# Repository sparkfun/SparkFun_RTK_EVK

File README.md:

SparkFun RTK EVK
========================================

[*SparkFun RTK EVK (GPS-24342)*](https://www.sparkfun.com/sparkfun-rtk-evk.html)

Designed and manufactured in Boulder, Colorado, USA, the SparkFun RTK Evaluation Kit is the perfect development platform for your fixed or mobile high-precision positioning and navigation needs. In terms of connectivity, the SparkFun RTK EVK has the lot: WiFi / BT, Ethernet and cellular!

Under the hood, the RTK EVK is based on the Espressif ESP32-WROVER processor with 16MB flash and 8MB PSRAM. The GNSS is the excellent dual-band ZED-F9P from u-blox. The u-blox NEO-D9S provides L-Band reception and access to correction services such as PointPerfect. The u-blox LARA-R6001D provides worldwide cellular connectivity; insert your nano SIM into the front panel and away you go! A WIZnet W5500 provides 10 / 100 megabit Ethernet connectivity. Data storage is micro-SD. The OLED display is 128x64 pixels. The EVK supports multiple power options, including: USB-C; Power over Ethernet (PoE); and DC voltages in the range 9V - 36V. 

Documentation
--------------

* **[Hookup Guide](http://docs.sparkfun.com/SparkFun_RTK_EVK/)** - Hookup Guide for the RTK EVK hosted by GitHub pages.
* **[RTK Everywhere Product Manual](https://docs.sparkfun.com/SparkFun_RTK_Everywhere_Firmware/)** - RTK Everywhere product manual hosted by GitHub Pages.

*Need to download or print our hookup guide?*

* [Print *(Print to PDF)* from Single-Page View](http://docs.sparkfun.com/SparkFun_RTK_EVK/print_view)

Repository Contents
-------------------

* **[/docs](/docs/)** - Online documentation files
    * **[assets](/docs/assets/)** - Assets files
        * **[RTK_EVK_Enclosure](/docs/assets/RTK_EVK_Enclosure/)**
            * **[/Front_Panel](/Front_Panel/)** - Eagle design files (.brd, .sch) for the prototype (PCB) enclosure panel used to validate the dimensions
            * **[/Front_Sticker](/Front_Sticker/)** - DXF and PDF files for the front sticker
            * **[/Rear_Panel](/Rear_Panel/)** - Eagle design files (.brd, .sch) for the prototype (PCB) enclosure panel used to validate the dimensions
            * **[/Rear_Sticker](/Rear_Sticker/)** - DXF and PDF files for the rear sticker
        * **[board_files](/docs/assets/board_files/)** - Files for the product design
        * **[img/](/docs/assets/img/hookup_guide/)** - Images for hookup guide documentation
* **[/Example_Sketches](/Example_Sketches/)** - Arduino IDE code examples
* **[/Hardware](/Hardware/)** - Eagle design files (.brd, .sch)
* **[/Production](/Production/)** - PCB panel production files

Firmware
----------------

The RTK Everywhere firmware has its own [dedicated repo](https://github.com/sparkfun/SparkFun_RTK_Everywhere_Firmware) as listed below.

* **[RTK Everywhere Firmware](https://github.com/sparkfun/SparkFun_RTK_Everywhere_Firmware)**
* **[RTK Everywhere Firmware Binaries](https://github.com/sparkfun/SparkFun_RTK_Everywhere_Firmware_Binaries)**

Product Variants
----------------

* [GPS-24342](https://www.sparkfun.com/sparkfun-rtk-evk.html)- v1.1, Initial Release

Version History
---------------

* v1.1- Initial Release

License Information
-------------------

This product is ***open source***!

Please review the [LICENSE.md](./LICENSE.md) file for license information.

If you have any questions or concerns about licensing, please contact technical support on our [SparkFun forums](https://forum.sparkfun.com/viewforum.php?f=152).

Distributed as-is; no warranty is given.

- Your friends at SparkFun.

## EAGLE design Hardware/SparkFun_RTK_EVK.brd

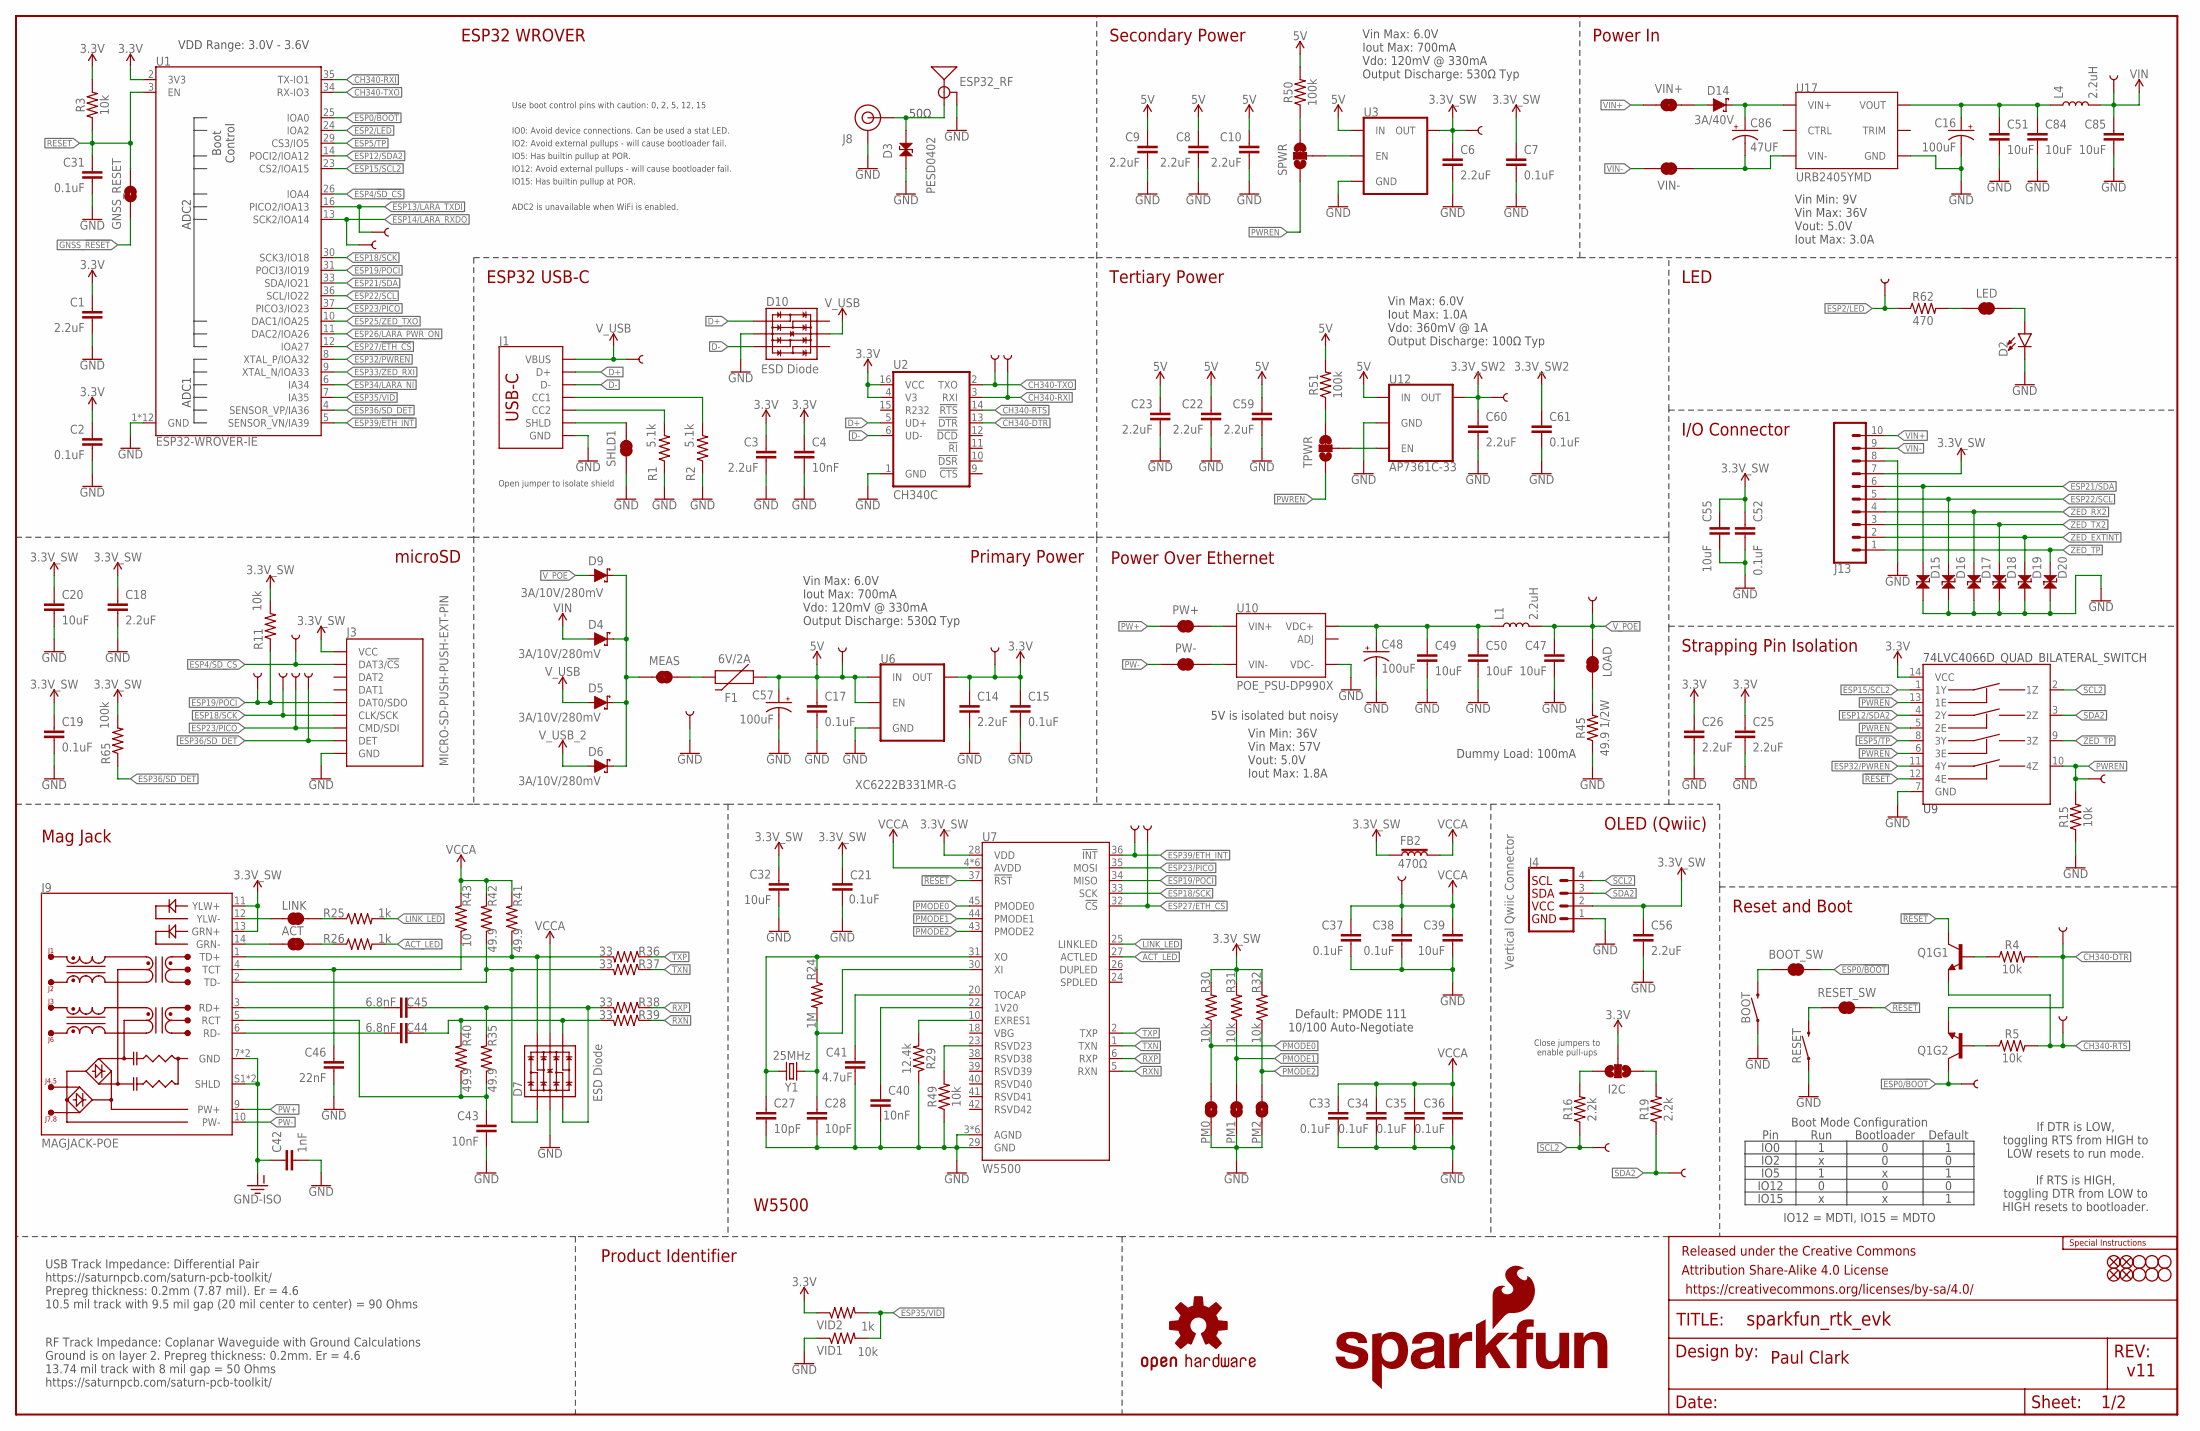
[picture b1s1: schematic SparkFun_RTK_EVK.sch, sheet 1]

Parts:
3V3, 3V3_SW, 3V3_SW2, 5V: TEST-POINTPOGO_PTH; 1X01_NO_SILK
ACT: JUMPER-SMT_2_NC_TRACE_SILK; SMT-JUMPER_2_NC_TRACE_SILK
BOOT: MOMENTARY-SWITCH-SPST-PTH-RIGHT-ANGLE-8-020; TACTILE_SWITCH_PTH_RA_8-020
BOOT_SW: JUMPER-SMT_2_NC_TRACE_SILK; SMT-JUMPER_2_NC_TRACE_SILK
C1, C3, C6, C8, C9, C10, C14, C18, C22, C23, C25, C26, C56, C59, C60: 2.2uF; 0603
C2, C7, C15, C17, C19, C21, C31, C33, C34, C35, C36, C37, C38, C52, C61: 0.1uF; 0603
C4, C40, C43: 10nF; 0603
C16, C48, C57: 100uF; PANASONIC_D
C20, C32, C39, C55: 10uF; 0603
C27, C28: 10pF; 0603
C41: 4.7uF; 0603
C42: 1nF; 1206
C44, C45: 6.8nF; 0603
C46: 22nF; 0603
C47, C49, C50, C51, C84, C85: 10uF; 0805
C86: 47UF; PANASONIC_D
D2: LED-RIGHT-ANGLE-PTH-GREEN; CBI-RIGHT-ANGLE-PTH
D3: PESD0402; 0402
D4, D5, D6, D9: 3A/10V/280mV; SOD-323
D7, D10: ESD Diode; SOT-23-6
D14: 3A/40V; SMA-DIODE
D15, D16, D17, D18, D19, D20: PESD0402-0402; 0402
DET: TEST-POINTPOGO_PTH; 1X01_NO_SILK
DTR: TEST-POINTPOGO_PTH; 1X01_NO_SILK
ESP32_RF: ANTENNA-SMA-GROUNDEDEDGE_RPSMA; RP-SMA-EDGE
ETH_CS: TEST-POINTPOGO_PTH; 1X01_NO_SILK
ETH_INT: TEST-POINTPOGO_PTH; 1X01_NO_SILK
F1: 6V/2A; 1210
FB2: 470Ω; 0603
FD1, FD2, FD3, FD4: FIDUCIAL1X2; FIDUCIAL-1X2
FRAME1: FRAME-LEDGER; CREATIVE_COMMONS
GND: TEST-POINTPOGO_PTH; 1X01_NO_SILK
GNSS_RESET: JUMPER-COMBO_2_NO; COMBO-JUMPER_2_NO
H1, H2, H3, H4, H5, H6: STAND-OFFTIGHT; STAND-OFF-TIGHT
I2C: JUMPER-SMT_3_NO_SILK; SMT-JUMPER_3_NO_SILK
J1: USB_C_4-LAYER_PADS; USB-C-16P_4LAYER-PADS
J3: MICRO-SD-PUSH-PUSH-EXT-PIN; MICROSD-EXTERNALPIN
J4: Vertical Qwiic Connector; JST04_1MM_VERT
J8: U.FL2PIN-REDUCED-FOOTPRINT; U.FL_REDUCED_FOOTPRINT
J9: MAGJACK-POE; MAGJACK-SYM_LED
J13: CONN_10_3.5MM_RA_HEADER; 1X10_SCREW_TERMINAL_3.5MM
L1, L4: 2.2uH; 0805-WIDE
LED: JUMPER-SMT_2_NC_TRACE_SILK; SMT-JUMPER_2_NC_TRACE_SILK
LINK: JUMPER-SMT_2_NC_TRACE_SILK; SMT-JUMPER_2_NC_TRACE_SILK
LOAD: JUMPER-SMT_2_NC_TRACE_SILK; SMT-JUMPER_2_NC_TRACE_SILK
LOGO1: SPECIAL_INSTRUCTIONS-ORDERING; ORDERING_INSTRUCTIONS
LOGO4: OSHW-LOGOS; OSHW-LOGO-S
LOGO5: SFE_LOGO_NAME.2_INCH; SFE_LOGO_NAME_.2
LOGO6: SFE_LOGO_FLAME.2_INCH; SFE_LOGO_FLAME_.2
MEAS: JUMPER-COMBO_2_NC_TRACE; COMBO-JUMPER_2_NC_TRACE
PICO: TEST-POINTPOGO_PTH; 1X01_NO_SILK
PM0, PM1, PM2: JUMPER-SMT_2_NO_SILK; SMT-JUMPER_2_NO_SILK
POCI: TEST-POINTPOGO_PTH; 1X01_NO_SILK
PW+: JUMPER-COMBO_2_NC_TRACE; COMBO-JUMPER_2_NC_TRACE
PW-: JUMPER-COMBO_2_NC_TRACE; COMBO-JUMPER_2_NC_TRACE
PWREN: TEST-POINTPOGO_PTH; 1X01_NO_SILK
Q1: TRANS_NPN_DUAL-MBT3904DW1T1; SC70-6
R1, R2: 5.1k; 0603
R3, R4, R5, R11, R15, R30, R31, R32, R49: 10k; 0603
R16, R19: 2.2k; 0603
R24: 1M; 0603
R25, R26: 1k; 0603
R29: 12.4k; 0603
R35, R40, R41, R42: 49.9; 0603
R36, R37, R38, R39: 33; 0603
R43: 10; 0603
R45: 49.9 1/2W; 1206
R50, R51, R65: 100k; 0603
R62: 470; 0603
RESET: MOMENTARY-SWITCH-SPST-PTH-RIGHT-ANGLE-8-020; TACTILE_SWITCH_PTH_RA_8-020
RESET_SW: JUMPER-SMT_2_NC_TRACE_SILK; SMT-JUMPER_2_NC_TRACE_SILK
RTS: TEST-POINTPOGO_PTH; 1X01_NO_SILK
RX: TEST-POINTPOGO_PTH; 1X01_NO_SILK
RXD: TEST-POINTPOGO_PTH; 1X01_NO_SILK
SCK: TEST-POINTPOGO_PTH; 1X01_NO_SILK
SCL2: TEST-POINTPOGO_PTH; 1X01_NO_SILK
SDA2: TEST-POINTPOGO_PTH; 1X01_NO_SILK
SD_CS: TEST-POINTPOGO_PTH; 1X01_NO_SILK
SHLD1: JUMPER-SMT_2_NC_TRACE_SILK; SMT-JUMPER_2_NC_TRACE_SILK
SPWR: JUMPER-SMT_3_1-NC_TRACE_SILK; SMT-JUMPER_3_1-NC_TRACE_SILK
TPWR: JUMPER-SMT_3_1-NC_TRACE_SILK; SMT-JUMPER_3_1-NC_TRACE_SILK
TP_BOOT: TEST-POINTPOGO_PTH; 1X01_NO_SILK
TP_LED: TEST-POINTPOGO_PTH; 1X01_NO_SILK
TX: TEST-POINTPOGO_PTH; 1X01_NO_SILK
TXD: TEST-POINTPOGO_PTH; 1X01_NO_SILK
U1: ESP32-WROVER-IE; ESP32-WROVER-E/IE
U2: CH340C; SO016
U3, U6: XC6222B331MR-G; SOT23-5
U7: W5500; LQFP-48
U9: 74LVC4066D_QUAD_BILATERAL_SWITCH; SO14
U10: POE_PSU-DP990X; DP990X
U12: AP7361C-33; UDFN-8
U17: URB2405YMD; URB_YMD-15WR3
VCCA: TEST-POINTPOGO_PTH; 1X01_NO_SILK
VID1: 10k; 0603
VID2: 1k; 0603
VIN: TEST-POINTPOGO_PTH; 1X01_NO_SILK
VIN+: JUMPER-COMBO_2_NC_TRACE; COMBO-JUMPER_2_NC_TRACE
VIN-: JUMPER-COMBO_2_NC_TRACE; COMBO-JUMPER_2_NC_TRACE
VPOE: TEST-POINTPOGO_PTH; 1X01_NO_SILK
VUSB: TEST-POINTPOGO_PTH; 1X01_NO_SILK
Y1: 25MHz; CRYSTAL-SMD-2.0X1.6MM

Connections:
3.3V: 3V3.1, C1.1, C2.1, C3.1, C4.1, C14.1, C15.1, C25.1, C26.1, I2C.2, R3.2, U1.2 (3V3), U2.4 (V3), U2.16 (VCC), U6.5 (OUT), U9.14 (VCC), VID2.1
3.3V_SW: 3V3_SW.1, C6.1, C7.1, C18.1, C19.1, C20.1, C21.1, C32.1, C52.1, C55.1, C56.1, FB2.1, J3.4 (VCC), J4.2, J9.11 (YLW+), J9.13 (GRN+), J13.7, R11.2, R30.2, R31.2, R32.2, R65.2, U3.5 (OUT), U7.28 (VDD); also elsewhere on the board
3.3V_SW2: 3V3_SW2.1, C60.1, C61.1, U12.1 (OUT); also elsewhere on the board
5V: 5V.1, C8.1, C9.1, C10.1, C17.1, C22.1, C23.1, C57.+, C59.1, F1.1, R50.2, R51.2, U3.1 (IN), U6.1 (IN), U6.3 (EN), U12.8 (IN); also elsewhere on the board
5V_RAW: C48.+, C49.1, C50.1, L1.1, U10.1 (VDC+), U10.2 (VDC+)
5V_RAW1: C16.+, C51.1, C84.1, L4.1, U17.4 (VOUT)
!RESET!: C31.1, GNSS_RESET.2, GNSS_RESET.4 (2), Q1.3 (C), R3.1, RESET_SW.1, U1.3 (EN), U7.37 (!RST!), U9.12 (4E)
ACT: ACT.1, J9.14 (GRN-)
ACT_LED: R26.2, U7.27 (ACTLED)
CH340-DTR: DTR.1, Q1.1 (E), R4.2, U2.13 (!DTR)
CH340-RTS: Q1.4 (E), R5.2, RTS.1, U2.14 (!RTS)
CH340-RXI: TX.1, U1.35 (TX-IO1), U2.3 (RXI)
CH340-TXO: RX.1, U1.34 (RX-IO3), U2.2 (TXO)
D+: D10.1 (IO1), J1.A6 (D+), J1.B6 (D+), U2.5 (UD+)
D-: D10.3 (IO2), J1.A7 (D-), J1.B7 (D-), U2.6 (UD-)
ESP0/!BOOT!: BOOT_SW.1, Q1.6 (C), TP_BOOT.1, U1.25 (IOA0)
ESP2/LED: R62.1, TP_LED.1, U1.24 (IOA2)
ESP4/!SD_CS!: J3.2 (DAT3/!CS!), SD_CS.1, U1.26 (IOA4)
ESP5/TP: U1.29 (CS3/IO5), U9.8 (3Y)
ESP12/SDA2: U1.14 (POCI2/IOA12), U9.4 (2Y)
ESP13/LARA_TXDI: TXD.1, U1.16 (PICO2/IOA13); also elsewhere on the board
ESP14/LARA_RXDO: RXD.1, U1.13 (SCK2/IOA14); also elsewhere on the board
ESP15/SCL2: U1.23 (CS2/IOA15), U9.1 (1Y)
ESP18/SCK: J3.5 (CLK/SCK), SCK.1, U1.30 (SCK3/IO18), U7.33 (SCK)
ESP19/POCI: J3.7 (DAT0/SDO), POCI.1, R11.1, U1.31 (POCI3/IO19), U7.34 (MISO)
ESP21/SDA: D15.1, J13.6, U1.33 (SDA/IO21); also elsewhere on the board
ESP22/SCL: D16.1, J13.5, U1.36 (SCL/IO22); also elsewhere on the board
ESP23/PICO: J3.3 (CMD/SDI), PICO.1, U1.37 (PICO3/IO23), U7.35 (MOSI)
ESP25/ZED_TXO: U1.10 (DAC1/IOA25); also elsewhere on the board
ESP26/LARA_PWR_ON: U1.11 (DAC2/IOA26); also elsewhere on the board
ESP27/!ETH_CS!: ETH_CS.1, U1.12 (IOA27), U7.32 (!CS!)
ESP32/PWREN: U1.8 (XTAL_P/IOA32), U9.11 (4Y)
ESP33/ZED_RXI: U1.9 (XTAL_N/IOA33); also elsewhere on the board
ESP34/LARA_NI: U1.6 (IA34); also elsewhere on the board
ESP35/VID: U1.7 (IA35), VID1.2, VID2.2
ESP36/SD_DET: DET.1, J3.9 (DET), R65.1, U1.4 (SENSOR_VP/IA36)
ESP39/!ETH_INT!: ETH_INT.1, U1.5 (SENSOR_VN/IA39), U7.36 (!INT!)
GND: BOOT.1, C1.2, C2.2, C3.2, C4.2, C6.2, C7.2, C8.2, C9.2, C10.2, C14.2, C15.2, C16.-, C17.2, C18.2, C19.2, C20.2, C21.2, C22.2, C23.2, C25.2, C26.2, C27.2, C28.2, C31.2, C32.2, C33.2, C34.2, C35.2, C36.2, C37.2, C38.2, C39.2, C40.2, C41.2, C42.2, C43.2, C46.2, C47.2, C48.-, C49.2, C50.2, C51.2, C52.2, C55.2, C56.2, C57.-, C59.2, C60.2, C61.2, C84.2, C85.2, D2.C, D3.2, D7.2 (VSS), D10.2 (VSS), D15.2, D16.2, D17.2, D18.2, D19.2, D20.2, ESP32_RF.GND@0 (GND), ESP32_RF.GND@1 (GND), ESP32_RF.GND@2 (GND), ESP32_RF.GND@3 (GND), GND.1, J1.GND, J1.GND2 (GND), J3.6 (GND), J3.10 (GND), J3.11 (GND), J3.12 (GND), J3.13 (GND), J4.1, J8.1 (GND), J8.2 (GND), J13.8, PM0.1, PM1.1, PM2.1, R1.1, R2.1, R15.1, R29.1, R45.1, R49.1, RESET.1, SHLD1.1, U1.1 (GND), U1.15 (GND), U1.38 (GND), U1.GND, U1.GNDT1 (GND), U1.GNDT2 (GND), U1.GNDT3 (GND), U1.GNDT4 (GND), U1.GNDT5 (GND), U1.GNDT6 (GND), U1.GNDT7 (GND), U1.GNDT8 (GND), U2.1 (GND), U3.2 (GND), U6.2 (GND), U7.3 (AGND), U7.9 (AGND), U7.14 (AGND), U7.16 (AGND), U7.19 (AGND)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; also elsewhere on the board
GND-ISO: C42.1, J9.7 (GND), J9.8 (GND), J9.S1 (SHLD), J9.S2 (SHLD)
GNSS_!RESET!: GNSS_RESET.1, GNSS_RESET.3 (1); also elsewhere on the board
LINK: J9.12 (YLW-), LINK.1
LINK_LED: R25.2, U7.25 (LINKLED)
MEAS: D4.C, D5.C, D6.C, D9.C, MEAS.2, MEAS.4 (2)
unnamed: J1.B5 (CC2), R1.2
unnamed: J1.A5 (CC1), R2.2
unnamed: Q1.2 (B), R5.1
unnamed: Q1.5 (B), R4.1
unnamed: LED.2, R62.2
unnamed: F1.2, MEAS.1, MEAS.3 (1)
unnamed: ACT.2, R26.1
unnamed: D3.1, ESP32_RF.SIG (SIGNAL), J8.FEED (SIGNAL)
unnamed: I2C.3, R16.2
unnamed: I2C.1, R19.2
unnamed: C27.1, R24.1, U7.31 (XO), Y1.1
unnamed: C28.1, R24.2, U7.30 (XI), Y1.3 (2)
unnamed: LINK.2, R25.1
unnamed: R50.1, SPWR.3
unnamed: R29.2, U7.10 (EXRES1)
unnamed: C40.1, U7.22 (1V20)
unnamed: C41.1, U7.20 (TOCAP)
unnamed: SPWR.2, U3.3 (EN)
unnamed: LOAD.1, R45.2
unnamed: RESET.2, RESET_SW.2
unnamed: BOOT.2, BOOT_SW.2
unnamed: R49.2, U7.23 (RSVD23)
unnamed: R51.1, TPWR.3
unnamed: TPWR.2, U12.5 (EN)
unnamed: D2.A, LED.1
PMODE0: PM0.2, R30.1, U7.45 (PMODE0)
PMODE1: PM1.2, R31.1, U7.44 (PMODE1)
PMODE2: PM2.2, R32.1, U7.43 (PMODE2)
PW1+: PW+.1, PW+.3 (1), U10.5 (VIN+), U10.6 (VIN+)
PW1-: PW-.1, PW-.3 (1), U10.7 (VIN-), U10.8 (VIN-)
PW+: J9.9 (PW+), PW+.2, PW+.4 (2)
PW-: J9.10 (PW-), PW-.2, PW-.4 (2)
PWREN: PWREN.1, R15.2, SPWR.1, TPWR.1, U9.5 (2E), U9.6 (3E), U9.10 (4Z), U9.13 (1E)
RCT: C43.1, J9.5 (RCT), R35.1, R40.1
RD+: C45.2, J9.3 (RD+)
RD-: C44.2, J9.6 (RD-)
RXN: R39.1, U7.5 (RXN)
RXN1: C44.1, D7.4 (IO3), R39.2, R40.2
RXP: R38.1, U7.6 (RXP)
RXP1: C45.1, D7.3 (IO2), R35.2, R38.2
SCL2: J4.4, R16.1, SCL2.1, U9.2 (1Z)
SDA2: J4.3, R19.1, SDA2.1, U9.3 (2Z)
SHIELD: J1.SHLD1 (SHLD), J1.SHLD2 (SHLD), J1.SHLD3 (SHLD), J1.SHLD4 (SHLD), SHLD1.2
TCT: C46.1, J9.4 (TCT), R43.1
TD+: D7.6 (IO4), J9.1 (TD+), R36.2, R41.1
TD-: D7.1 (IO1), J9.2 (TD-), R37.2, R42.1
TXN: R37.1, U7.1 (TXN)
TXP: R36.1, U7.2 (TXP)
VCCA: C33.1, C34.1, C35.1, C36.1, C37.1, C38.1, C39.1, D7.5 (VCC), FB2.2, R41.2, R42.2, R43.2, U7.4 (AVDD), U7.8 (AVDD), U7.11 (AVDD), U7.15 (AVDD), U7.17 (AVDD), U7.21 (AVDD), VCCA.1
VIN: C85.1, D4.A, L4.2, VIN.1
VIN1+: D14.A, VIN+.1, VIN+.3 (1)
VIN1-: C86.-, U17.2 (VIN-), VIN-.2, VIN-.4 (2)
VIN2+: C86.+, D14.C, U17.3 (VIN+)
VIN+: J13.10, VIN+.2, VIN+.4 (2)
VIN-: J13.9, VIN-.1, VIN-.3 (1)
V_POE: C47.1, D9.A, L1.2, LOAD.2, VPOE.1
V_USB: D5.A, D10.5 (VCC), J1.VBUS1 (VBUS), J1.VBUS2 (VBUS), VUSB.1
V_USB_2: D6.A; also elsewhere on the board
ZED_EXTINT: D19.1, J13.2; also elsewhere on the board
ZED_RX2: D17.1, J13.4; also elsewhere on the board
ZED_TP: D20.1, J13.1, U9.9 (3Z); also elsewhere on the board
ZED_TX2: D18.1, J13.3; also elsewhere on the board

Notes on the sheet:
ESP32 WROVER
ESP32 USB-C
Paul Clark
v11
Reset and Boot
LED
Secondary Power
Primary Power
microSD
Strapping Pin Isolation
W5500
Mag Jack
VDD Range: 3.0V - 3.6V
Vin Max: 6.0V Iout Max: 700mA Vdo: 120mV @ 330mA Output Discharge: 530Ω Typ
If DTR is LOW, toggling RTS from HIGH to LOW resets to run mode. If RTS is HIGH, toggling DTR from LOW to HIGH resets to bootloader.
Pin
IO0
IO2
IO12
IO15
IO5
Run
Bootloader
Default
IO12 = MDTI, IO15 = MDTO
Boot Mode Configuration
IO0: Avoid device connections. Can be used a stat LED.
ADC2 is unavailable when WiFi is enabled.
IO12: Avoid external pullups - will cause bootloader fail.
Use boot control pins with caution: 0, 2, 5, 12, 15
IO2: Avoid external pullups - will cause bootloader fail.
IO15: Has builtin pullup at POR.
IO5: Has builtin pullup at POR.
Close jumpers to enable pull-ups
Open jumper to isolate shield
RF Track Impedance: Coplanar Waveguide with Ground Calculations Ground is on layer 2. Prepreg thickness: 0.2mm. Er = 4.6 13.74 mil track with 8 mil gap = 50 Ohms https://saturnpcb.com/saturn-pcb-toolkit/
USB Track Impedance: Differential Pair https://saturnpcb.com/saturn-pcb-toolkit/ Prepreg thickness: 0.2mm (7.87 mil). Er = 4.6 10.5 mil track with 9.5 mil gap (20 mil center to center) = 90 Ohms
50Ω
Power Over Ethernet
5V is isolated but noisy

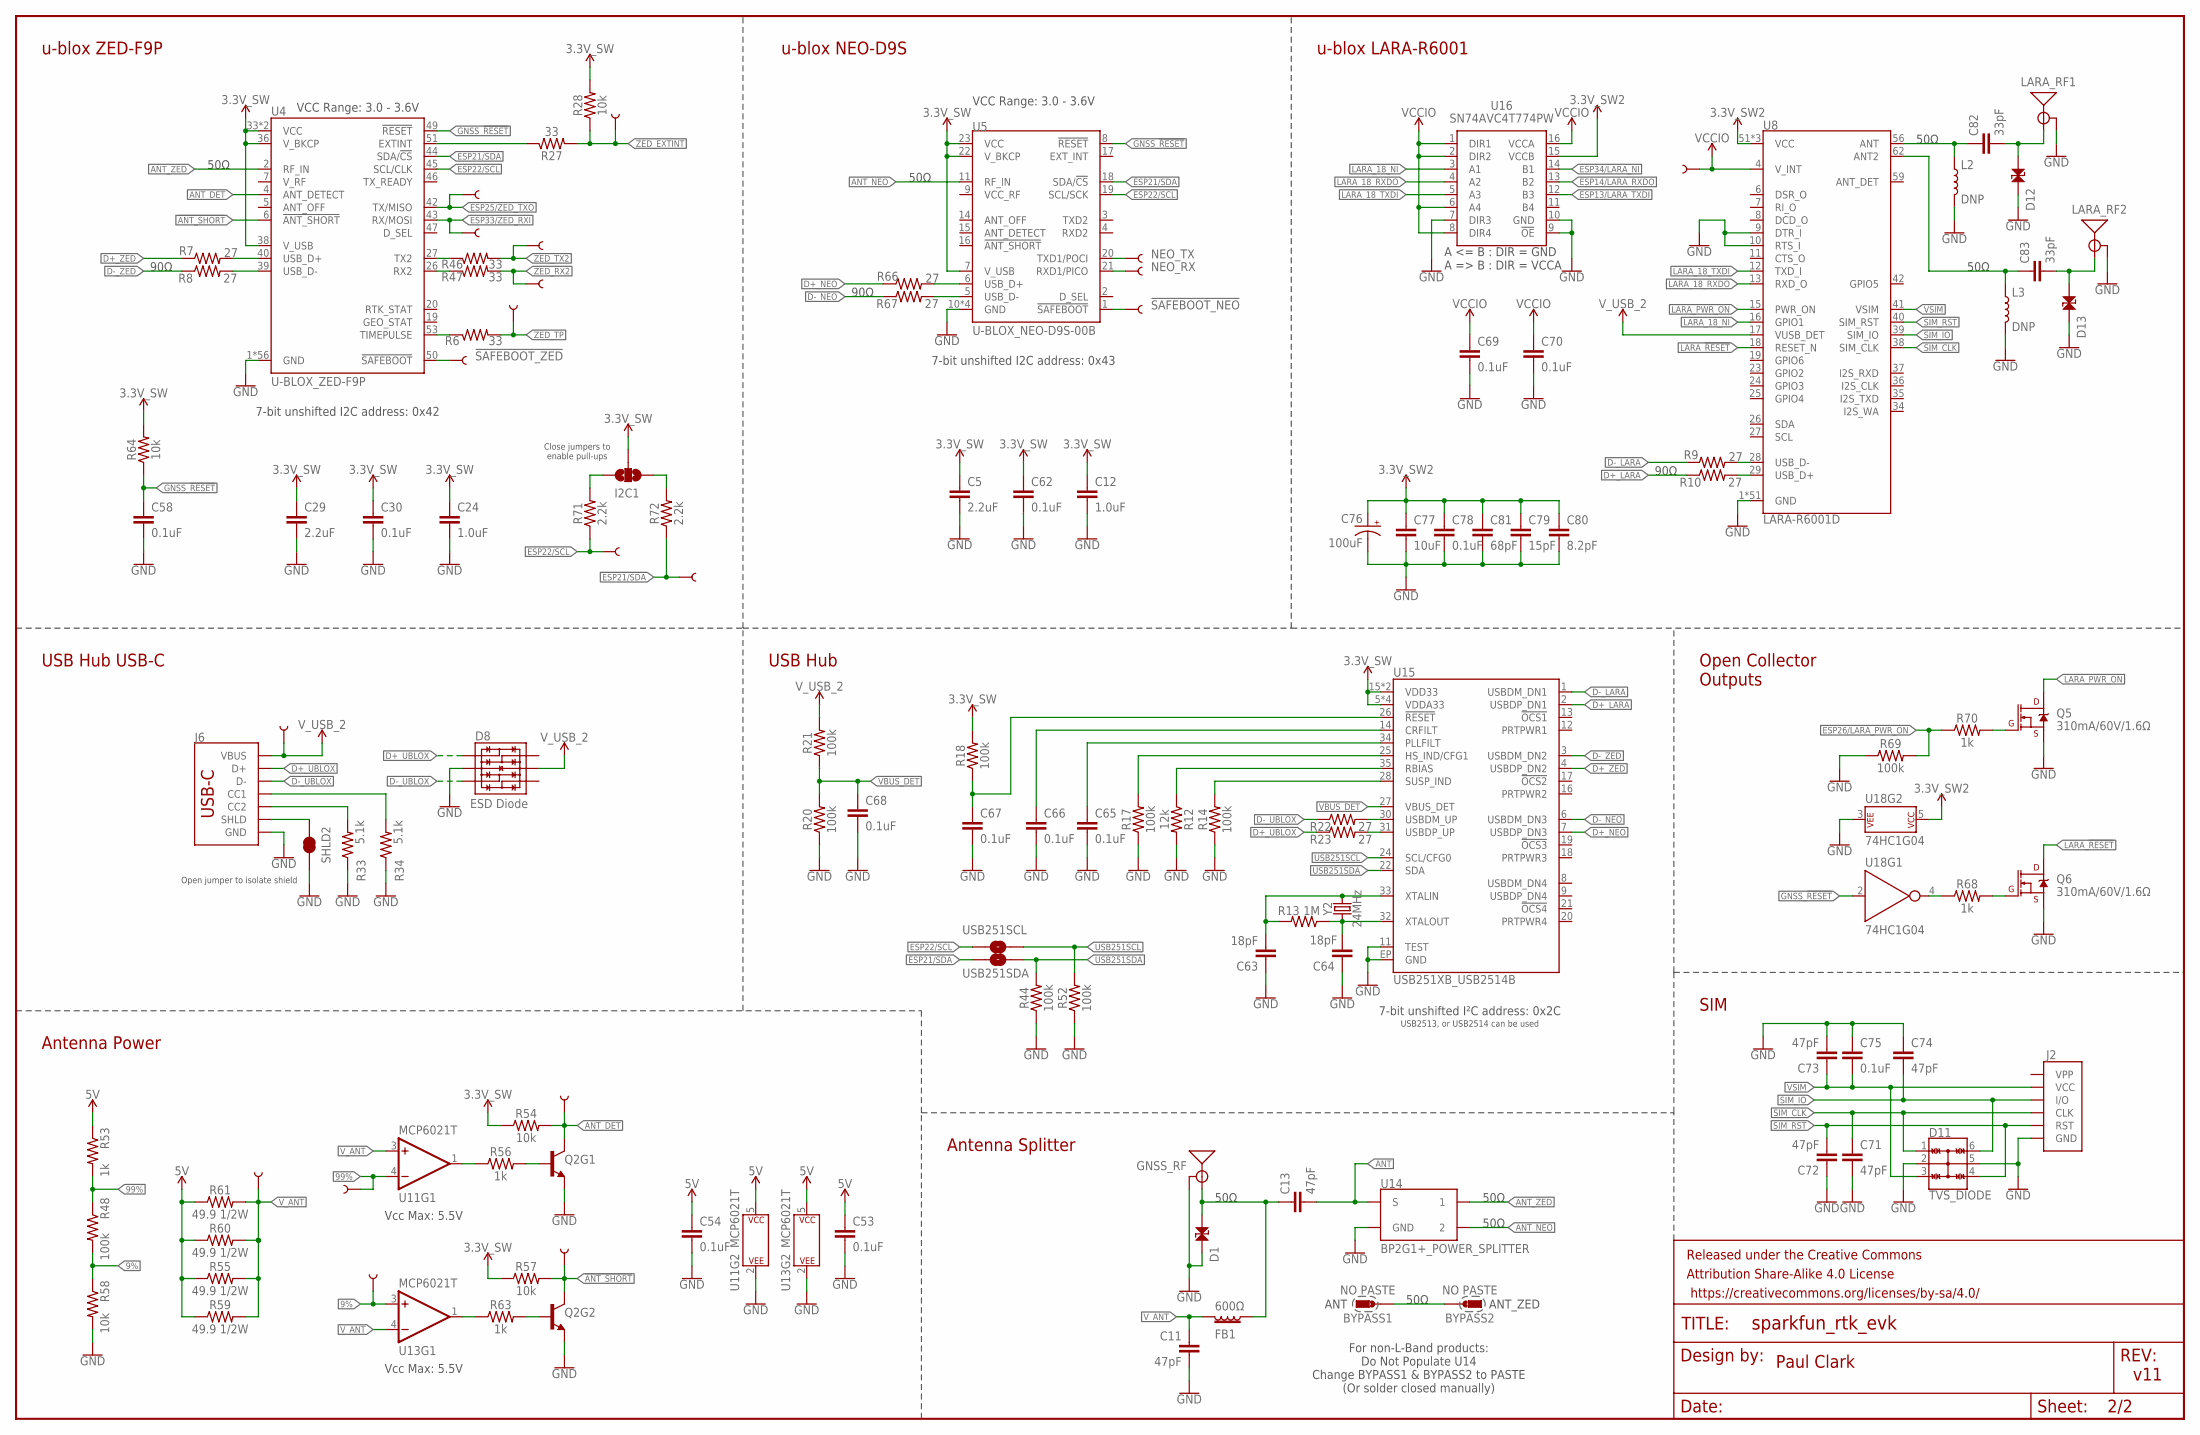
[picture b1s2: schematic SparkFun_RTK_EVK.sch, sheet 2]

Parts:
9%, 99%: TEST-POINTPOGO_PTH; 1X01_NO_SILK
!SAFEBOOT_NEO!: TEST-POINTPOGO_PTH; 1X01_NO_SILK
!SAFEBOOT_ZED!: TEST-POINTPOGO_PTH; 1X01_NO_SILK
ANT_DET: TEST-POINTPOGO_PTH; 1X01_NO_SILK
ANT_SHT: TEST-POINTPOGO_PTH; 1X01_NO_SILK
BYPASS1, BYPASS2: NO PASTE; SMT-JUMPER_2_SOIC-PAD_NO-PASTE
C5, C29: 2.2uF; 0603
C11, C13, C71, C72, C73, C74: 47pF; 0603
C12, C24: 1.0uF; 0603
C30, C53, C54, C58, C62, C65, C66, C67, C68, C69, C70, C75, C78: 0.1uF; 0603
C63, C64: 18pF; 0603
C76: 100uF; PANASONIC_D
C77: 10uF; 0805
C79: 15pF; 0603
C80: 8.2pF; 0603
C81: 68pF; 0603
C82, C83: 33pF; 0603
D1, D12, D13: PESD0402-0402; 0402
D8: ESD Diode; SOT-23-6
D11: TVS_DIODE; SOT23-6L
FB1: 600Ω; 0805
FRAME2: FRAME-LEDGERNO_FOOTPRINT; DUMMY
GNSS_RF: ANTENNA-SMA-GROUNDEDEDGE_SMA; SMA-EDGE
I2C1: JUMPER-SMT_3_NO_SILK; SMT-JUMPER_3_NO_SILK
J2: SIMHOLDER-PUSHPUSH; NANO_SIM_PP
J6: USB_C_4-LAYER_PADS; USB-C-16P_4LAYER-PADS
L2, L3: DNP; 0603_NO-CREAM
LARA_RF1, LARA_RF2: ANTENNA-SMA-GROUNDEDEDGE_SMA; SMA-EDGE
NEO_RX: TEST-POINTPOGO_PTH; 1X01_NO_SILK
NEO_TX: TEST-POINTPOGO_PTH; 1X01_NO_SILK
Q2: TRANS_NPN_DUAL-MBT3904DW1T1; SC70-6
Q5, Q6: 310mA/60V/1.6Ω; SOT323
R6, R27, R46, R47: 33; 0603
R7, R8, R9, R10, R22, R23, R66, R67: 27; 0603
R12: 12k; 0603
R13: 1M; 0603
R14, R17, R18, R20, R21, R44, R48, R52, R69: 100k; 0603
R28, R54, R57, R58, R64: 10k; 0603
R33, R34: 5.1k; 0603
R53, R56, R63, R68, R70: 1k; 0603
R55, R59, R60, R61: 49.9 1/2W; 1206
R71, R72: 2.2k; 0603
RX2: TEST-POINTPOGO_PTH; 1X01_NO_SILK
SCL: TEST-POINTPOGO_PTH; 1X01_NO_SILK
SDA: TEST-POINTPOGO_PTH; 1X01_NO_SILK
SHLD2: JUMPER-SMT_2_NC_TRACE_SILK; SMT-JUMPER_2_NC_TRACE_SILK
TP: TEST-POINTPOGO_PTH; 1X01_NO_SILK
TX2: TEST-POINTPOGO_PTH; 1X01_NO_SILK
U4: U-BLOX_ZED-F9P; ZED-F9P
U5: U-BLOX_NEO-D9S-00B; NEO-M9N/M8T/M8U/D9S
U8: LARA-R6001D; LARA-LGA
U11, U13: MCP6021T; SOT23-5
U14: BP2G1+_POWER_SPLITTER; XX21
U15: USB251XB_USB2514B; QFN-36
U16: SN74AVC4T774PW; SOP65P640X120-16N
U18: 74HC1G04; SOT353
USB251SCL, USB251SDA: JUMPER-SMT_2_NO_SILK; SMT-JUMPER_2_NO_SILK
VANT: TEST-POINTPOGO_PTH; 1X01_NO_SILK
VCCIO: TEST-POINTPOGO_PTH; 1X01_NO_SILK
VUSB2: TEST-POINTPOGO_PTH; 1X01_NO_SILK
Y2: 24MHz; CRYSTAL-SMD-2.0X1.6MM
ZED_EXTINT: TEST-POINTPOGO_PTH; 1X01_NO_SILK
ZED_RXI: TEST-POINTPOGO_PTH; 1X01_NO_SILK
ZED_TXO: TEST-POINTPOGO_PTH; 1X01_NO_SILK

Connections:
3.3V_SW: C5.1, C12.1, C24.1, C29.1, C30.1, C62.1, I2C1.2, R18.2, R28.2, R54.1, R57.1, R64.2, U4.33 (VCC), U4.34 (VCC), U4.36 (V_BKCP), U4.38 (V_USB), U5.7 (V_USB), U5.22 (V_BKCP), U5.23 (VCC), U15.5 (VDDA33), U15.10 (VDDA33), U15.15 (VDD33), U15.23 (VDD33), U15.29 (VDDA33), U15.36 (VDDA33); also elsewhere on the board
3.3V_SW2: C76.+, C77.1, C78.1, C79.1, C80.1, C81.1, U8.51 (VCC), U8.52 (VCC), U8.53 (VCC), U16.15 (VCCB), U18.5 (P$V+); also elsewhere on the board
5V: C53.1, C54.1, R53.1, R55.1, R59.1, R60.1, R61.1, U11.5 (P$V+), U13.5 (P$V+); also elsewhere on the board
9%: 9%.1, R48.2, R58.1, U13.3 (+IN)
99%: 99%.1, R48.1, R53.2, U11.4 (-IN)
!ANT_SHORT!: ANT_SHT.1, Q2.6 (C), R57.2, U4.6 (!ANT_SHORT!)
!SAFEBOOT_NEO!: !SAFEBOOT_NEO!.1, U5.1 (!SAFEBOOT!)
!SAFEBOOT_ZED!: !SAFEBOOT_ZED!.1, U4.50 (!SAFEBOOT!)
ANT: C13.2, U14.2 (S)
ANT_DET: ANT_DET.1, Q2.3 (C), R54.2, U4.4 (ANT_DETECT)
ANT_NEO: U5.11 (RF_IN), U14.5 (2)
ANT_ZED: U4.2 (RF_IN), U14.8 (1)
BYPASS: BYPASS1.1, BYPASS2.1
D+_LARA: R10.1, U15.2 (USBDP_DN1)
D+_NEO: R66.1, U15.7 (USBDP_DN3)
D+_UBLOX: D8.1 (IO1), J6.A6 (D+), J6.B6 (D+), R23.1
D+_ZED: R7.1, U15.4 (USBDP_DN2)
D-_LARA: R9.1, U15.1 (USBDM_DN1)
D-_NEO: R67.1, U15.6 (USBDM_DN3)
D-_UBLOX: D8.3 (IO2), J6.A7 (D-), J6.B7 (D-), R22.1
D-_ZED: R8.1, U15.3 (USBDM_DN2)
ESP13/LARA_TXDI: U16.12 (B3); also elsewhere on the board
ESP14/LARA_RXDO: U16.13 (B2); also elsewhere on the board
ESP21/SDA: R72.1, SDA.1, U4.44 (SDA/!CS!), U5.18 (SDA/!CS!), USB251SDA.1; also elsewhere on the board
ESP22/SCL: R71.1, SCL.1, U4.45 (SCL/CLK), U5.19 (SCL/SCK), USB251SCL.1; also elsewhere on the board
ESP25/ZED_TXO: U4.42 (TX/MISO), ZED_TXO.1; also elsewhere on the board
ESP26/LARA_PWR_ON: R69.2, R70.1; also elsewhere on the board
ESP33/ZED_RXI: U4.43 (RX/MOSI), ZED_RXI.1; also elsewhere on the board
ESP34/LARA_NI: U16.14 (B1); also elsewhere on the board
GND: C5.2, C11.2, C12.2, C24.2, C29.2, C30.2, C53.2, C54.2, C58.2, C62.2, C63.1, C64.1, C65.2, C66.2, C67.2, C68.2, C69.2, C70.2, C71.2, C72.1, C73.2, C74.1, C75.1, C76.-, C77.2, C78.2, C79.2, C80.2, C81.2, D1.2, D8.2 (VSS), D11.2, D11.5, D12.2, D13.2, GNSS_RF.GND@0 (GND), GNSS_RF.GND@1 (GND), GNSS_RF.GND@2 (GND), GNSS_RF.GND@3 (GND), J2.C5 (GND), J6.GND, J6.GND2 (GND), L2.2, L3.2, LARA_RF1.GND@0 (GND), LARA_RF1.GND@1 (GND), LARA_RF1.GND@2 (GND), LARA_RF1.GND@3 (GND), LARA_RF2.GND@0 (GND), LARA_RF2.GND@1 (GND), LARA_RF2.GND@2 (GND), LARA_RF2.GND@3 (GND), Q2.1 (E), Q2.4 (E), Q5.2 (S), Q6.2 (S), R12.2, R14.1, R17.1, R20.1, R33.1, R34.1, R44.1, R52.1, R58.2, R69.1, SHLD2.1, U4.1 (GND), U4.3 (GND), U4.12 (GND), U4.14 (GND), U4.32 (GND), U4.37 (GND), U4.41 (GND), U4.48 (GND), U4.55 (GND), U4.56 (GND), U4.57 (GND), U4.58 (GND), U4.59 (GND), U4.60 (GND), U4.61 (GND), U4.62 (GND), U4.63 (GND), U4.64 (GND), U4.65 (GND), U4.66 (GND), U4.67 (GND), U4.68 (GND), U4.69 (GND), U4.70 (GND), U4.71 (GND), U4.72 (GND), U4.73 (GND), U4.74 (GND), U4.75 (GND), U4.76 (GND), U4.77 (GND), U4.78 (GND), U4.79 (GND), U4.80 (GND), U4.81 (GND), U4.82 (GND), U4.83 (GND), U4.84 (GND), U4.85 (GND), U4.86 (GND), U4.87 (GND), U4.88 (GND)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; also elsewhere on the board
GNSS_!RESET!: C58.1, R64.1, U4.49 (!RESET!), U5.8 (!RESET!), U18.2 (A); also elsewhere on the board
LARA_18_NI: U8.16 (GPIO1), U16.3 (A1)
LARA_18_RXDO: U8.13 (RXD_O), U16.4 (A2)
LARA_18_TXDI: U8.12 (TXD_I), U16.5 (A3)
LARA_!RESET!: Q6.3 (D), U8.18 (RESET_N)
LARA_PWR_ON: Q5.3 (D), U8.15 (PWR_ON)
unnamed: R7.2, U4.40 (USB_D+)
unnamed: R8.2, U4.39 (USB_D-)
unnamed: J6.SHLD1 (SHLD), J6.SHLD2 (SHLD), J6.SHLD3 (SHLD), J6.SHLD4 (SHLD), SHLD2.2
unnamed: R27.1, U4.51 (EXTINT)
unnamed: R46.1, U4.27 (TX2)
unnamed: R68.1, U18.4 (Y)
unnamed: R66.2, U5.6 (USB_D+)
unnamed: R67.2, U5.5 (USB_D-)
unnamed: R47.1, U4.26 (RX2)
unnamed: J6.B5 (CC2), R33.2
unnamed: J6.A5 (CC1), R34.2
unnamed: R56.1, U11.1 (OUT)
unnamed: R6.1, U4.53 (TIMEPULSE)
unnamed: Q2.5 (B), R56.2
unnamed: Q2.2 (B), R63.2
unnamed: R63.1, U13.1 (OUT)
unnamed: Q6.1 (G), R68.2
unnamed: I2C1.3, R71.2
unnamed: I2C1.1, R72.2
unnamed: R9.2, U8.28 (USB_D-)
unnamed: R10.2, U8.29 (USB_D+)
unnamed: C63.2, R13.2, U15.33 (XTALIN), Y2.3 (2)
unnamed: C64.2, R13.1, U15.32 (XTALOUT), Y2.1
unnamed: R12.1, U15.35 (RBIAS)
unnamed: R14.2, U15.28 (SUSP_IND)
unnamed: R17.2, U15.25 (HS_IND/CFG1)
unnamed: C65.1, U15.34 (PLLFILT)
unnamed: C66.1, U15.14 (CRFILT)
unnamed: R22.2, U15.30 (USBDM_UP)
unnamed: R23.2, U15.31 (USBDP_UP)
unnamed: C82.2, D12.1, LARA_RF1.SIG (SIGNAL)
unnamed: C82.1, L2.1, U8.56 (ANT)
unnamed: C83.2, D13.1, LARA_RF2.SIG (SIGNAL)
unnamed: C83.1, L3.1, U8.62 (ANT2)
unnamed: Q5.1 (G), R70.2
NEO_RXI: NEO_RX.1, U5.21 (RXD1/PICO)
NEO_TXO: NEO_TX.1, U5.20 (TXD1/POCI)
RF: C13.1, D1.1, FB1.2, GNSS_RF.SIG (SIGNAL)
SIM_CLK: C71.1, D11.1, J2.C3 (CLK), U8.38 (SIM_CLK)
SIM_IO: C74.2, D11.6, J2.C7 (I/O), U8.39 (SIM_IO)
SIM_RST: C72.2, D11.4, J2.C2 (RST), U8.40 (SIM_RST)
USB251SCL: R52.2, U15.24 (SCL/CFG0), USB251SCL.2
USB251SDA: R44.2, U15.22 (SDA), USB251SDA.2
USB_!RESET: C67.1, R18.1, U15.26 (!RESET)
VBUS_DET: C68.1, R20.2, R21.1, U15.27 (VBUS_DET)
VCCIO: C69.1, C70.1, U8.4 (V_INT), U16.1 (DIR1), U16.2 (DIR2), U16.6 (A4), U16.8 (DIR4), U16.16 (VCCA), VCCIO.1
VSIM: C73.1, C75.2, D11.3, J2.C1 (VCC), U8.41 (VSIM)
V_ANT: C11.1, FB1.1, R55.2, R59.2, R60.2, R61.2, U11.3 (+IN), U13.4 (-IN), VANT.1
V_USB_2: D8.5 (VCC), J6.VBUS1 (VBUS), J6.VBUS2 (VBUS), R21.2, U8.17 (VUSB_DET), VUSB2.1; also elsewhere on the board
ZED_EXTINT: R27.2, R28.1, ZED_EXTINT.1; also elsewhere on the board
ZED_RX2: R47.2, RX2.1; also elsewhere on the board
ZED_TP: R6.2, TP.1; also elsewhere on the board
ZED_TX2: R46.2, TX2.1; also elsewhere on the board

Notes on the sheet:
Vcc Max: 5.5V
50Ω
90Ω
u-blox ZED-F9P
VCC Range: 3.0 - 3.6V
u-blox LARA-R6001
Antenna Power
7-bit unshifted I2C address: 0x43
u-blox NEO-D9S
USB Hub USB-C
Open jumper to isolate shield
Antenna Splitter
7-bit unshifted I2C address: 0x42
7-bit unshifted I²C address: 0x2C
USB2513, or USB2514 can be used
USB Hub
SIM
Open Collector Outputs
Close jumpers to enable pull-ups
For non-L-Band products: Do Not Populate U14 Change BYPASS1 & BYPASS2 to PASTE (Or solder closed manually)
ANT
ANT_ZED
Paul Clark
v11

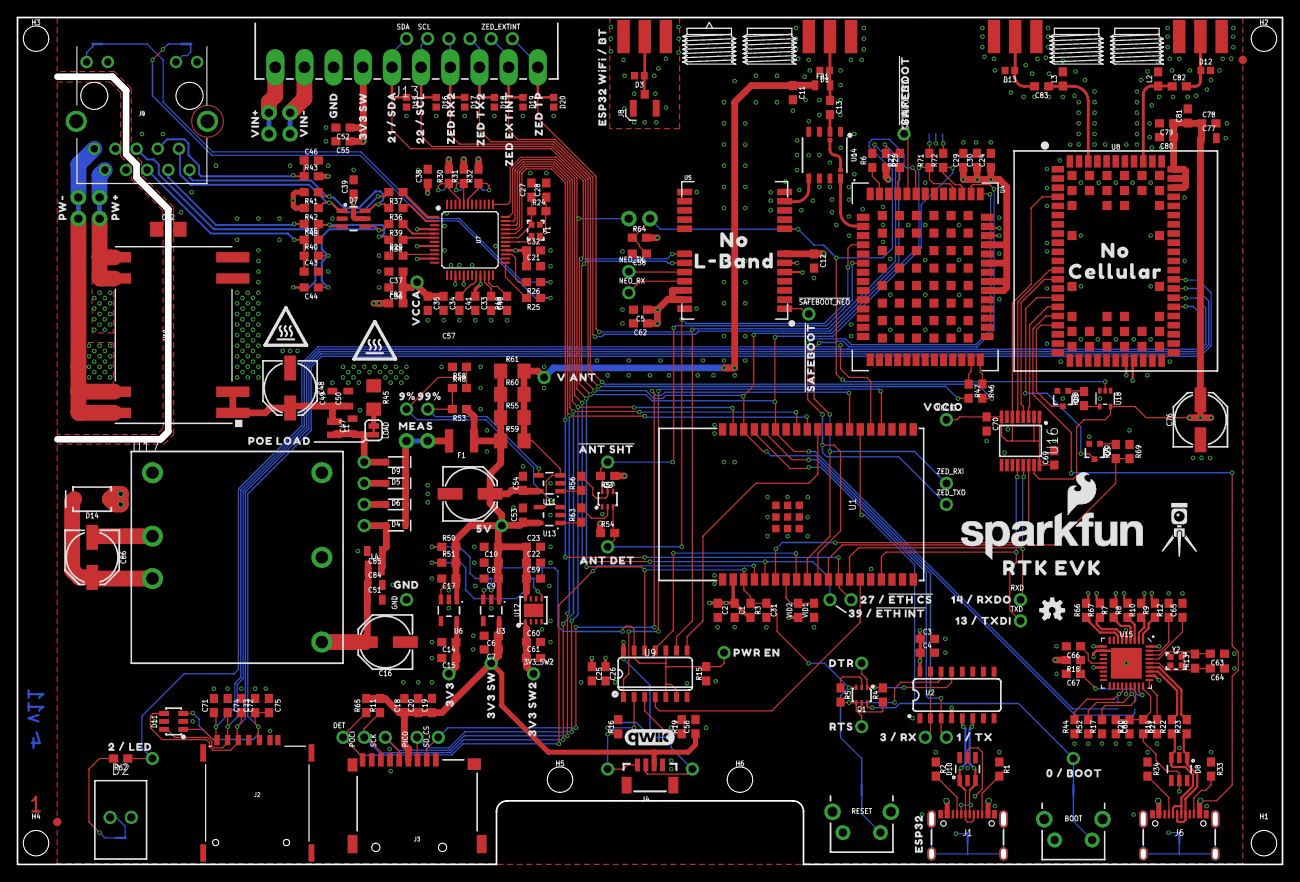
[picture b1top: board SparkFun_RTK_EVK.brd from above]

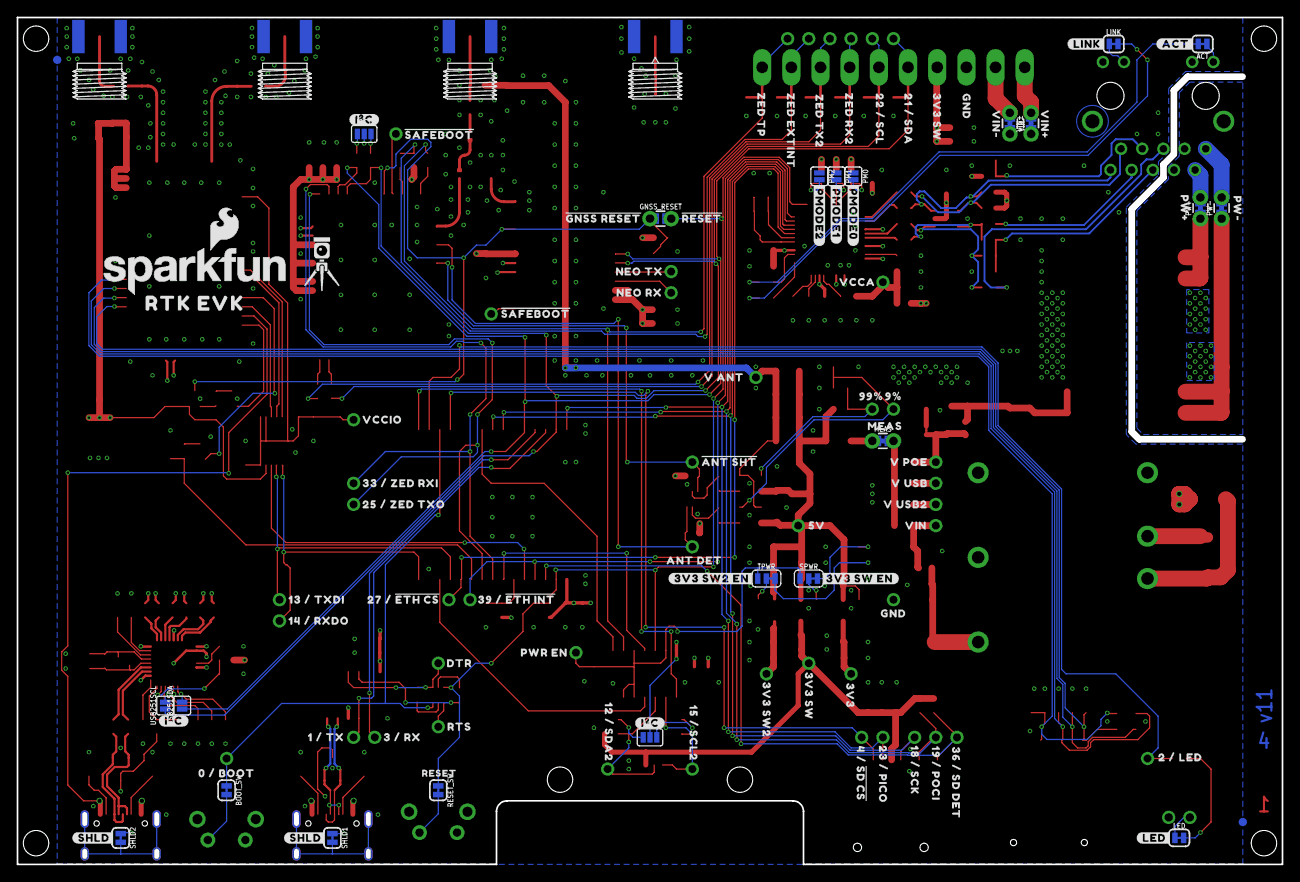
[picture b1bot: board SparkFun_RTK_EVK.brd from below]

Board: 4 copper layers, 151.8 x 101.6 mm, 435 parts (97 on the bottom side), 176 nets.

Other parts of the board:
LOGO2: QWIIC_LOGO_6MM; QWIIC_6MM
LOGO7: SFE_LOGO_NAME.2_INCH; SFE_LOGO_NAME_.2
LOGO8: SFE_LOGO_FLAME.2_INCH; SFE_LOGO_FLAME_.2
U$2: 33_#_ZED_RXI0
U$3, U$45: #SHLD#0
U$4, U$46, U$48: #I�C#0
U$5, U$113: PW#0
U$6, U$114: PW#1
U$7, U$149: 0_#_BOOT0
U$8, U$12, U$41, U$93: #SAFEBOOT#2226
U$9: #ACT#0
U$10: #LINK#1
U$11, U$13: RTK_EVK0
U$14: NEO_TX2
U$15: NEO_RX3
U$16, U$18: GND2
U$17, U$65: 3V3_SW20
U$19: 12_#_SDA20
U$20: 15_#_SCL213
U$21: ESP32_WIFI_#_BT0
U$22, U$23: 3V3_SW3
U$24, U$107: VCCA0
U$25, U$26: 21_#_SDA4
U$28, U$30: 22_#_SCL22
U$29, U$111: 27_#_#ETH_CS#0
U$31, U$32: ZED_RX223
U$33, U$36: ZED_TX2224
U$34, U$99: 1_#_TX20
U$35, U$100: 3_#_RX20
U$37, U$38: ZED_EXTINT2225
U$39, U$40: ZED_TP2226
U$42, U$94: ANT_DET2227
U$43, U$95: #ANT_SHT#2228
U$44, U$106: 9#2230
U$47, U$104: 99#2230
U$49, U$105: V_ANT2229
U$55, U$76: RTS2231
U$56, U$77: DTR2232
U$57, U$66: 2_#_LED0
U$58: #LED#2234
U$59, U$88: 3V3_SW25
U$60, U$87: 3V325
U$61, U$86: 5V25
U$62, U$84: MEAS2
U$63, U$70: VIN#0
U$64: 36_#_SD_DET0
U$67: #PMODE0#0
U$68: #PMODE1#1
U$69: #PMODE2#2
U$71, U$72: VIN#1
U$73, U$108: 14_#_RXDO0
U$74: #RESET#0
U$75, U$103: 13_#_TXDI15
U$78: ESP320
U$79, U$110: 39_#_#ETH_INT#0
U$80, U$141: PWR_EN2233
U$81: V_POE0
U$82: V_USB3
U$83: V_USB24
U$85: VIN1
U$89: 4_#_#SD_CS#15
U$90: 25_#_ZED_TXO0
U$91, U$92: NO0
U$96: CELLULAR2
U$97: L#BAND1
U$98: 23_#_PICO23
U$101: 19_#_POCI19
U$102: 18_#_SCK6
U$115, U$116: VCCIO0
U$117: #3V3_SW_EN#0
U$118: #3V3_SW2_EN#0
U$135, U$143: GND12
U$136: POE_LOAD0
U$146, U$147: HIGH_TEMP_WARNING
U$148: RESET0
U$152, U$153: RTK5#SVG0
U$154: #GNSS_RESET#0

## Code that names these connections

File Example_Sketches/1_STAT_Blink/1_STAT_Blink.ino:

/*
  SparkFun RTK EVK Test Sketch

  License: MIT. Please see LICENSE.md for more details

  ESP32-WROVER-IE Pin Allocations:
  D0  : Boot + Boot Button
  D1  : Serial TX (CH340 RX)
  D2  : STAT LED
  D3  : Serial RX (CH340 TX)
  D4  : SD CS
  D5  : GNSS Time Pulse - via 74HC4066 switch and PWREN
  D12 : SDA2 - Qwiic OLED - via 74HC4066 switch and PWREN
  D13 : Serial1 TX - LARA_TXDI
  D14 : Serial1 RX - LARA RXDO
  D15 : SCL2 - Qwiic OLED - via 74HC4066 switch and PWREN
  D16 : N/A
  D17 : N/A
  D18 : SPI SCK
  D19 : SPI POCI
  D21 : I2C SDA
  D22 : I2C SCL
  D23 : SPI PICO
  D25 : Serial2 RX - ZED-F9P TXO
  D26 : LARA Power On
  D27 : Ethernet Chip Select
  D32 : PWREN
  D33 : Serial2 TX - ZED-F9P RXI
  A34 : LARA Network Indicator
  A35 : Board Detect (3.0V)
  A36 : SD Card Detect
  A39 : Ethernet Interrupt
*/

const int STAT_LED = 2;
const int SD_CS = 4; // Chip select for the microSD card
const int GNSS_INT = 5; // ZED_F9P time pulse interrupt
const int SDA_2 = 12; // OLED
const int SERIAL1_TX = 13; // LARA_TXDI
const int SERIAL1_RX = 14; // LARA RXDO
const int SCL_2 = 15; // OLED
const int SDA_1 = 21; // ZED-F9P and NEO-D9S
const int SCL_1 = 22; // ZED-F9P and NEO-D9S
const int SERIAL2_RX = 25; // ZED-F9P TXO
const int LARA_PWR = 26; // LARA_PWR_ON - inverted - set LARA_PWR high to pull LARA_PWR_ON low
const int ETHERNET_CS = 27; // Chip select for the WizNet W5500
const int PWREN = 32; // 74HC4066 switch Enable - pull high to enable SCL2/SDA2 and GNSS_INT
const int SERIAL2_TX = 33; // ZED-F9P RXI
const int LARA_NI = 34; // LARA Network Indicator - only valid when the LARA is powered on
const int SD_PRESENT = 36; // microSD card card present - from the microSD socket switch
const int ETHERNET_INT = 39; // WizNet W5500 interrupt

void setup()
{
  pinMode(SD_CS, OUTPUT);
  digitalWrite(SD_CS, HIGH);
  pinMode(ETHERNET_CS, OUTPUT);
  digitalWrite(ETHERNET_CS, HIGH);
  pinMode(PWREN, OUTPUT);
  digitalWrite(PWREN, HIGH);

  pinMode(STAT_LED, OUTPUT);

}

void loop()
{
  digitalWrite(STAT_LED, !digitalRead(STAT_LED)); // Toggle the STAT LED
  delay(500); // At 1Hz
}

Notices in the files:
parts and their libraries:
SparkFun-Capacitors: Licensing: Creative Commons ShareAlike 4.0 International - https://creativecommons.org/licenses/by-sa/4.0
SparkFun-Aesthetics: Released under the Creative Commons Attribution Share-Alike 4.0 License
SparkFun-Aesthetics: https://creativecommons.org/licenses/by-sa/4.0
